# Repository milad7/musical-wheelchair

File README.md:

# musical-wheelchair
Musical Wheelchair is a fun project based on musical chairs game.Pick a number between 1 to 15 and let the Musical Wheelchair to play music and randomly stop on a numbered LED.

Part List:
1) Coin Cell Battery Holder - 20mm x 1
https://www.sparkfun.com/products/783

2) Mini Speaker - PC Mount 12mm 2.048kHz x 1
https://www.sparkfun.com/products/7950

3) AVR 8 Pin 20MHz 8K 4A/D - ATtiny85 x 1
https://www.sparkfun.com/products/9378

4) SPDT Mini Power Switch x 1
https://www.sparkfun.com/products/102

5) LED - Basic Red 5mm x 15
https://www.sparkfun.com/products/9590

6) DIP Sockets Solder Tail - 8-Pin x 1 (Optional)
https://www.sparkfun.com/products/7937

7) Header - 2x3 (Male, 0.1") x 1
https://www.sparkfun.com/products/12807
http://www.digikey.com/product-detail/en/amphenol-fci/67997-206HLF/609-3234-ND/1878491

8) 100 Ohm 1/4W 5% CF MINI x 4
http://www.digikey.ca/product-detail/en/stackpole-electronics-inc/CFM14JT100R/S100QCT-ND/2617658

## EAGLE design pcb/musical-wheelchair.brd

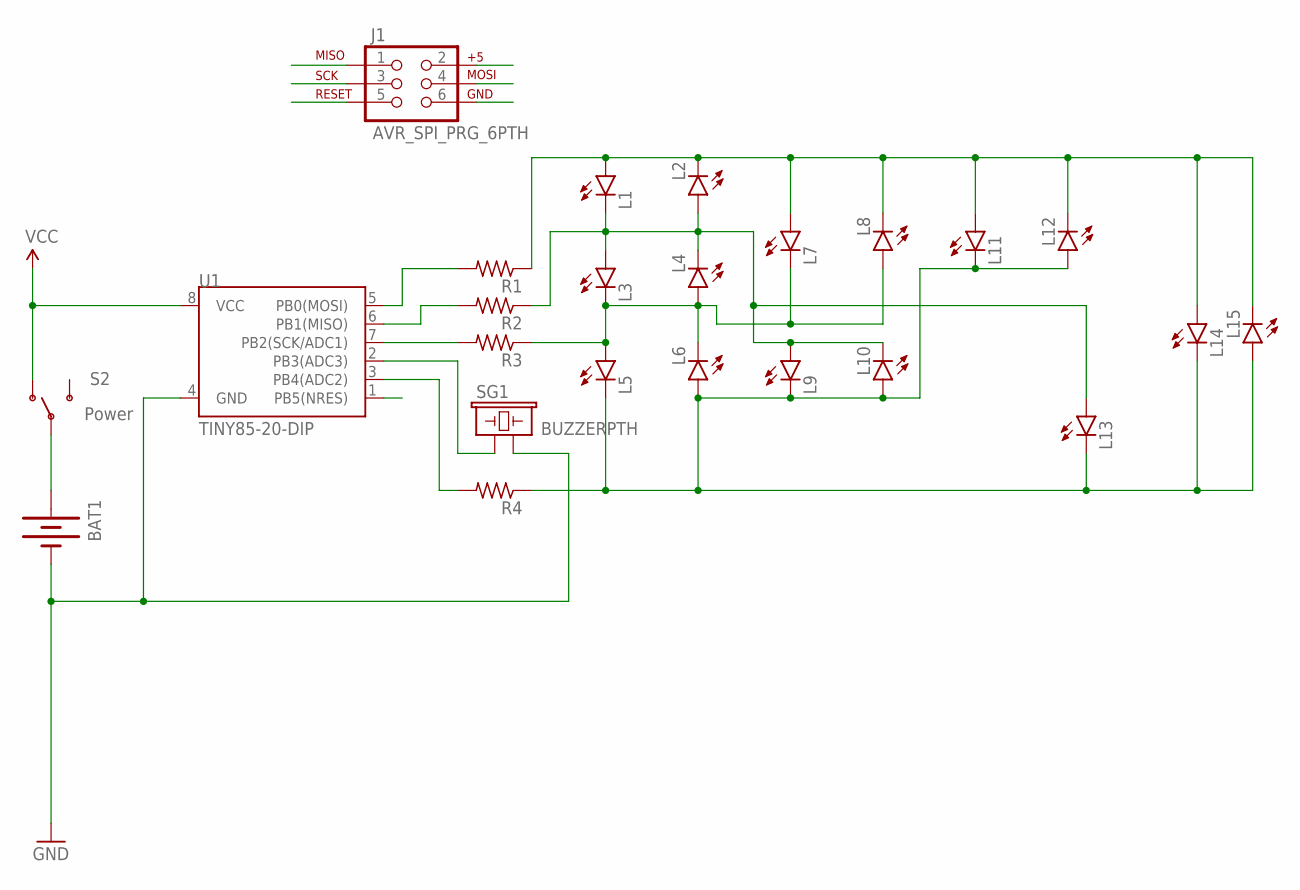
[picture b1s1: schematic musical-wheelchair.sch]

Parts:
BAT1: BATTERY20PTH; BATTCOM_20MM_PTH
J1: AVR_SPI_PRG_6PTH; 2X3
L1, L2, L3, L4, L5, L6, L7, L8, L9, L10, L11, L12, L13, L14, L15: LED5MM
R1, R2, R3, R4: R-US_0204/5; 0204/5
S2: Power; SWITCH-SPDT
SG1: BUZZERPTH; BUZZER-12MM
U1: TINY85-20-DIP; DIP08

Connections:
GND: BAT1.2 (-), J1.6, SG1.- (2), U1.4 (GND)
L12: L1.K (C), L2.A, L3.A, L4.K (C), L9.A, L10.K (C), L13.A, R2.1
MISO: J1.1, R2.2, U1.6 (PB1(MISO))
MOSI: J1.4, R1.2, U1.5 (PB0(MOSI))
unnamed: BAT1.1 (+), S2.2
unnamed: SG1.+ (1), U1.2 (PB3(ADC3))
unnamed: R4.2, U1.3 (PB4(ADC2))
unnamed: L1.A, L2.K (C), L7.A, L8.K (C), L11.A, L12.K (C), L14.A, L15.K (C), R1.1
unnamed: L3.K (C), L4.A, L5.A, L6.K (C), L7.K (C), L8.A, R3.1
unnamed: L5.K (C), L6.A, L9.K (C), L10.A, L11.K (C), L12.A, L13.K (C), L14.K (C), L15.A, R4.1
RST: J1.5, U1.1 (PB5(NRES))
SCK: J1.3, R3.2, U1.7 (PB2(SCK/ADC1))
VCC: J1.2, S2.1 (O), U1.8 (VCC)

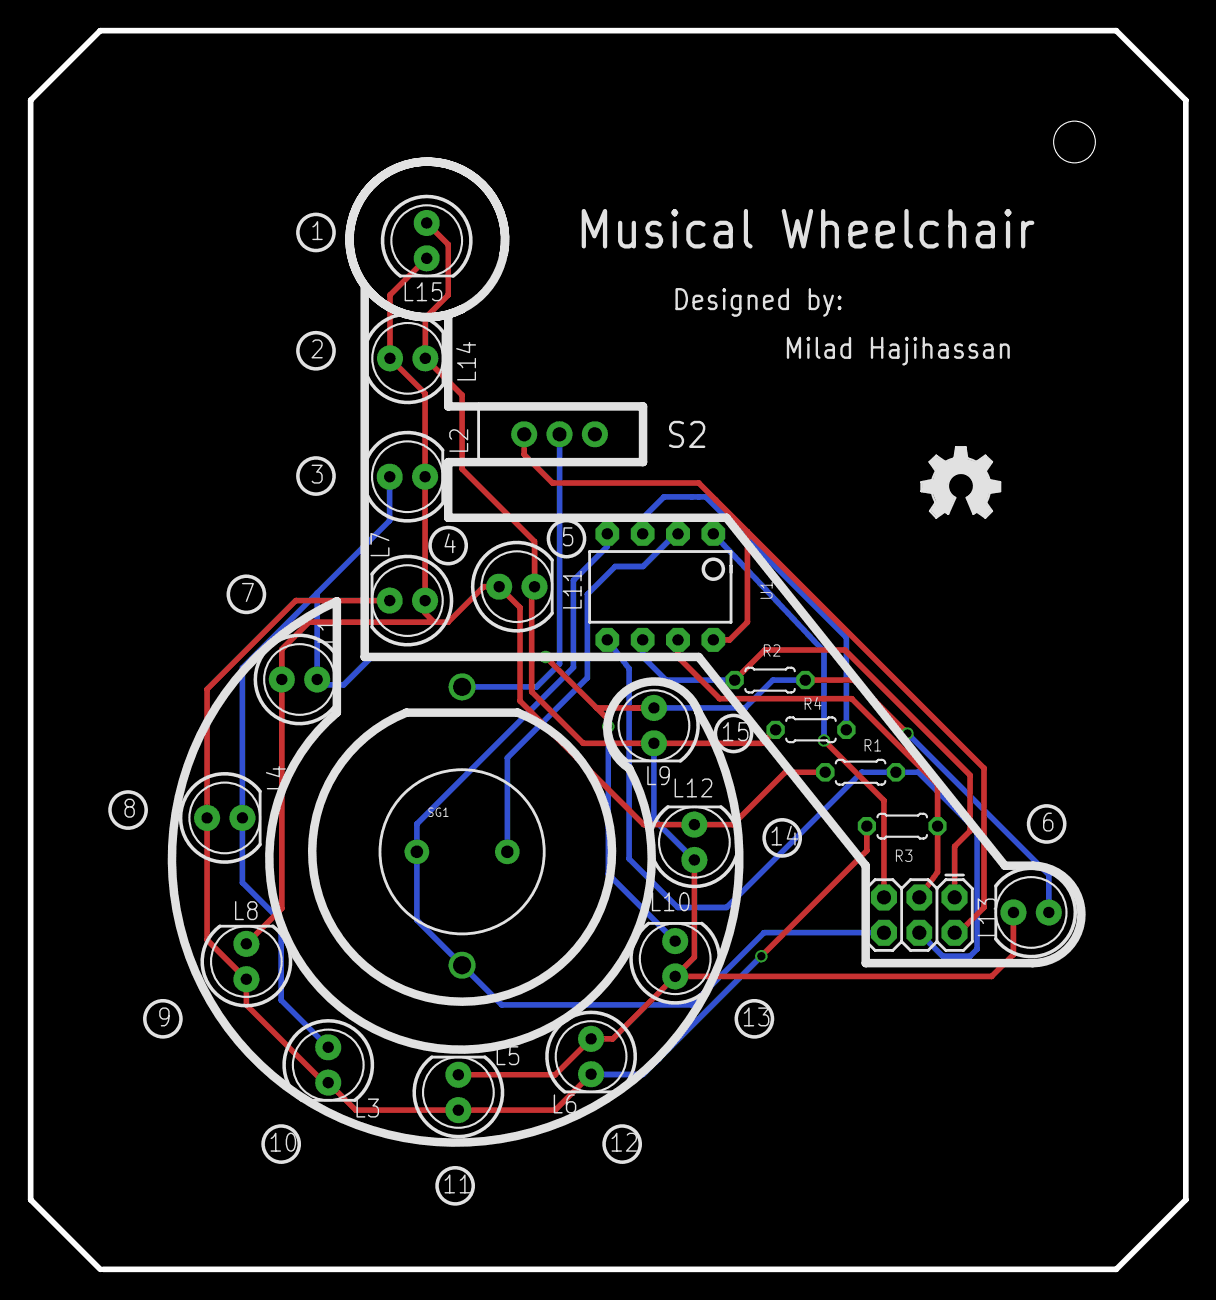
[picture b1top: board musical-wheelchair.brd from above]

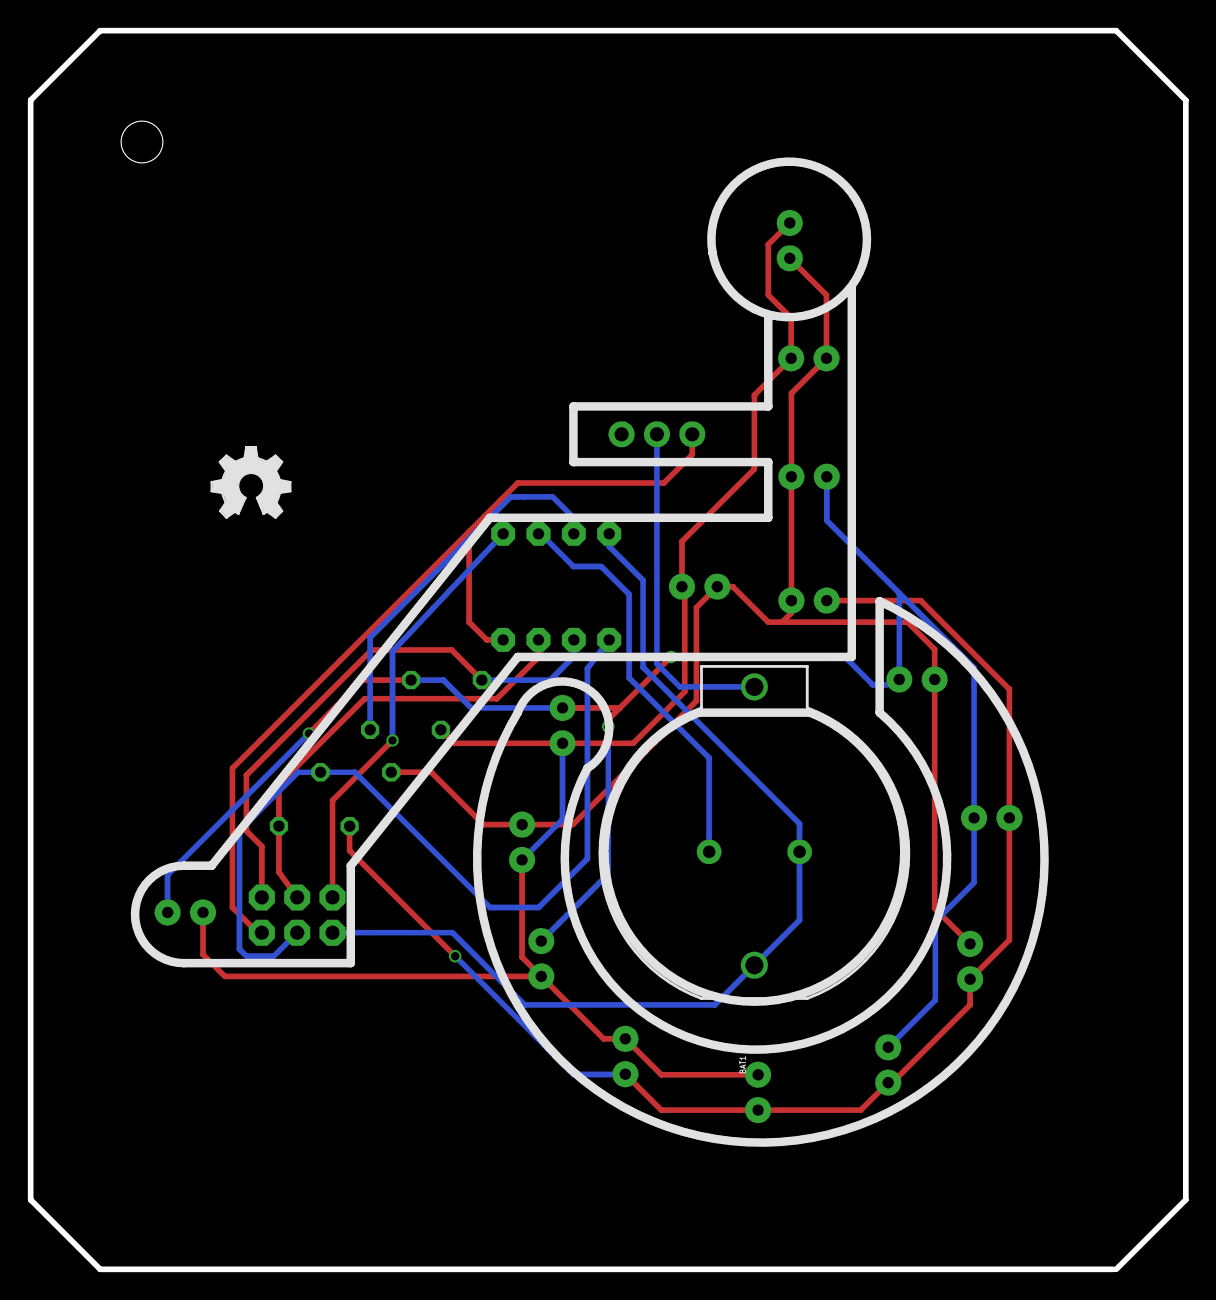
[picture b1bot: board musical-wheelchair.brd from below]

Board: 2 copper layers, 83.0 x 89.0 mm, 26 parts (2 on the bottom side), 13 nets.

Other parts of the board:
U$1, U$2: OSHW_FILLX200_NOTEXT

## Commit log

2017-01-18 Updated README.md
    Project details plus parts list was added.
2017-01-30 Added Eagle PCB board and schematic
2017-05-28 Added test image
2017-05-28 Updated readme file
2017-07-02 Added firmware
2017-08-16 no message
2017-08-17 Part list
2017-12-16 Update 8 bit tempos

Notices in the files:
parts and their libraries:
SparkFun: Licensing: CC v3.0 Share-Alike You are welcome to use this library for commercial purposes.
SparkFun-Electromechanical: Licensing: Creative Commons ShareAlike 4.0 International - https://creativecommons.org/licenses/by-sa/4.0
